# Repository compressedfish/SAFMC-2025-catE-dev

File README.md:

# SAFMC-2025-HW-Dev
meowmeowmeowmeowmeowmrowmeowmeowmeowmrowmeowmraaaaaaaaaaaaaaaaaaaaaaaaaa

pcb/keyboard     - general sensor and electronics assembly backplane thingy

pcb/cameraadapt  - testing board for OV2312/OV9782 RGB-IR camera modules

todo:
- design clip on mounting plates for cameras
- design camera mount
- test ov2312 sensor
- break out rpi5 serial interfaces

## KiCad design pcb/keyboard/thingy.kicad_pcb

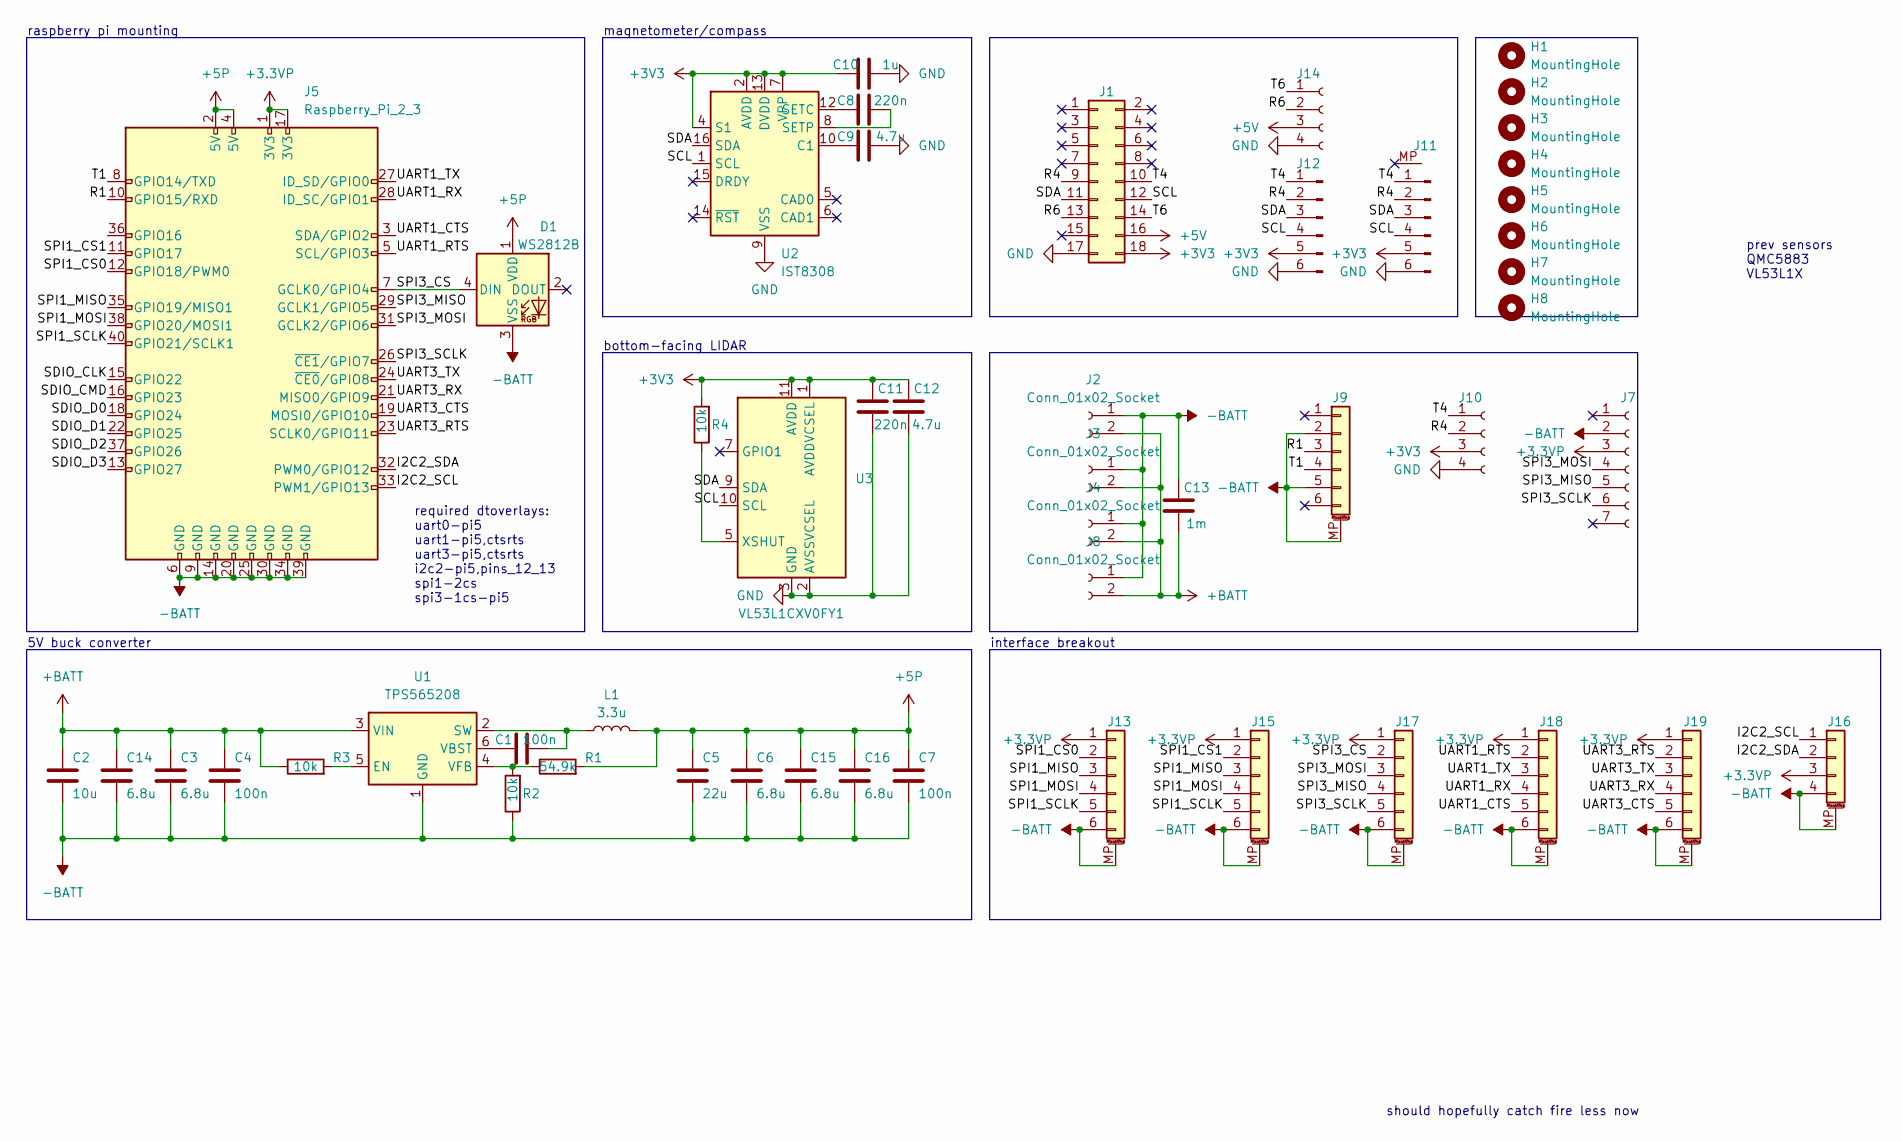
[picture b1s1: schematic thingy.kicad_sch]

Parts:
C1, C4, C7: 100n; C_0402_1005Metric
C2: 10u; CP_Elec_5x5.4
C3, C6, C14, C15, C16: 6.8u; C_0805_2012Metric
C5: 22u; CP_Elec_5x5.4
C8, C11: 220n; R_0603_1608Metric
C9, C12: 4.7u; R_0603_1608Metric
C10: 1u; R_0603_1608Metric
C13: 1m; CP_Radial_D8.0mm_P5.00mm
D1: WS2812B; LED_WS2812B-2020_PLCC4_2.0x2.0mm
H1, H2, H3, H4: MountingHole; MountingHole_2.2mm_M2
H5, H6, H7, H8: MountingHole; MountingHole_4.3mm_M4
J1: Conn_02x09_Odd_Even; PinHeader_2x09_P2.54mm_Vertical
J2, J3, J4, J8: Conn_01x02_Socket; XT-60_male
J5: Raspberry_Pi_2_3; PinSocket_2x20_P2.54mm_Horizontal
J7: Conn_01x07_Socket; PinSocket_1x07_P2.54mm_Vertical
J9: Conn_01x06_MountingPin; JST_SH_SM06B-SRSS-TB_1x06-1MP_P1.00mm_Horizontal
J10: Conn_01x04_Socket; PinHeader_1x04_P2.54mm_Vertical
J11: Conn_01x06_Pin; TE_Micro-MaTch_215079-6_2x03_P1.27mm_Vertical
J12: Conn_01x06_Pin; TE_84952-6_1x06-1MP_P1.0mm_Horizontal
J13, J15, J17, J18, J19: Conn_01x06; JST_SH_BM06B-SRSS-TB_1x06-1MP_P1.00mm_Vertical
J14: Conn_01x04_Socket; PinSocket_1x04_P2.54mm_Vertical
J16: Conn_01x04_MountingPin; JST_SH_BM04B-SRSS-TB_1x04-1MP_P1.00mm_Vertical
L1: 3.3u; L_Sunlord_MWSA0603S
R1: 54.9k; R_0402_1005Metric
R2, R3, R4: 10k; R_0402_1005Metric
U1: TPS565208; SOT-23-6
U2: IST8308; LGA-16_3x3mm_P0.5mm
U3: VL53L1CXV0FY1; ST_VL53L1x

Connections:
+3.3VP: J5.1 (3V3), J5.17 (3V3), J7.3, J13.1, J15.1, J16.3, J17.1, J18.1, J19.1
+3V3: C10.1, C11.1, C12.1, J1.18, J10.3, J11.5, J12.5, R4.2, U2.2 (AVDD), U2.4 (S1), U2.7 (VPP), U2.13 (DVDD), U3.1 (AVDDVCSEL), U3.11 (AVDD)
+5P: C5.1, C6.1, C7.1, C15.1, C16.1, D1.1 (VDD), J5.2 (5V), J5.4 (5V), L1.2, R1.2
+BATT: C2.1, C3.1, C4.1, C13.2, C14.1, J2.2, J3.2, J4.2, J8.2, R3.1, U1.3 (VIN)
-BATT: C2.2, C3.2, C4.2, C5.2, C6.2, C7.2, C13.1, C14.2, C15.2, C16.2, D1.3 (VSS), J2.1, J3.1, J4.1, J5.6 (GND), J5.9 (GND), J5.14 (GND), J5.20 (GND), J5.25 (GND), J5.30 (GND), J5.34 (GND), J5.39 (GND), J7.2, J8.1, J9.2, J9.5, J9.MP (MountPin), J13.6, J13.MP (MountPin), J15.6, J15.MP (MountPin), J16.4, J16.MP (MountPin), J17.6, J17.MP (MountPin), J18.6, J18.MP (MountPin), J19.6, J19.MP (MountPin), R2.1, U1.1 (GND)
/I2C2_SCL: J5.33 (PWM1/GPIO13), J16.1
/I2C2_SDA: J5.32 (PWM0/GPIO12), J16.2
/R1: J5.10 (GPIO15/RXD), J9.3
/R4: J1.9, J10.2, J11.2, J12.2
/R6: J1.13, J14.2
/SCL: J1.12, J11.4, J12.4, U2.1 (SCL), U3.10 (SCL)
/SDA: J1.11, J11.3, J12.3, U2.16 (SDA), U3.9 (SDA)
/SDIO_CLK: J5.15 (GPIO22)
/SDIO_CMD: J5.16 (GPIO23)
/SDIO_D0: J5.18 (GPIO24)
/SDIO_D1: J5.22 (GPIO25)
/SDIO_D2: J5.37 (GPIO26)
/SDIO_D3: J5.13 (GPIO27)
/SPI1_CS0: J5.12 (GPIO18/PWM0), J13.2
/SPI1_CS1: J5.11 (GPIO17), J15.2
/SPI1_MISO: J5.35 (GPIO19/MISO1), J13.3, J15.3
/SPI1_MOSI: J5.38 (GPIO20/MOSI1), J13.4, J15.4
/SPI1_SCLK: J5.40 (GPIO21/SCLK1), J13.5, J15.5
/SPI3_CS: D1.4 (DIN), J5.7 (GCLK0/GPIO4), J17.2
/SPI3_MISO: J5.29 (GCLK1/GPIO5), J7.5, J17.4
/SPI3_MOSI: J5.31 (GCLK2/GPIO6), J7.4, J17.3
/SPI3_SCLK: J5.26 (~CE1/GPIO7), J7.6, J17.5
/T1: J5.8 (GPIO14/TXD), J9.4
/T4: J1.10, J10.1, J11.1, J12.1
/T6: J1.14, J14.1
/UART1_CTS: J5.3 (SDA/GPIO2), J18.5
/UART1_RTS: J5.5 (SCL/GPIO3), J18.2
/UART1_RX: J5.28 (ID_SC/GPIO1), J18.4
/UART1_TX: J5.27 (ID_SD/GPIO0), J18.3
/UART3_CTS: J5.19 (MOSI0/GPIO10), J19.5
/UART3_RTS: J5.23 (SCLK0/GPIO11), J19.2
/UART3_RX: J5.21 (MISO0/GPIO9), J19.4
/UART3_TX: J5.24 (~CE0/GPIO8), J19.3
GND: C9.2, C10.2, C11.2, C12.2, J1.17, J10.4, J11.6, J12.6, J14.4, U2.9 (VSS), U2.11 (VSS), U3.2 (AVSSVCSEL), U3.3 (GND), U3.4 (GND), U3.6 (GND), U3.12 (GND)
unnamed: J1.16, J14.3
unnamed: R3.2, U1.5 (EN)
unnamed: C1.2, L1.1, U1.2 (SW)
unnamed: C1.1, U1.6 (VBST)
unnamed: R1.1, R2.2, U1.4 (VFB)
unnamed: C9.1, U2.10 (C1)
unnamed: C8.1, U2.12 (SETC)
unnamed: C8.2, U2.8 (SETP)
unnamed: R4.1, U3.5 (XSHUT)

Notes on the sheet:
prev sensors QMC5883 VL53L1X
interface breakout
raspberry pi mounting
5V buck converter
magnetometer/compass
required dtoverlays: uart0-pi5 uart1-pi5,ctsrts uart3-pi5,ctsrts i2c2-pi5,pins_12_13 spi1-2cs spi3-1cs-pi5
should hopefully catch fire less now
bottom-facing LIDAR

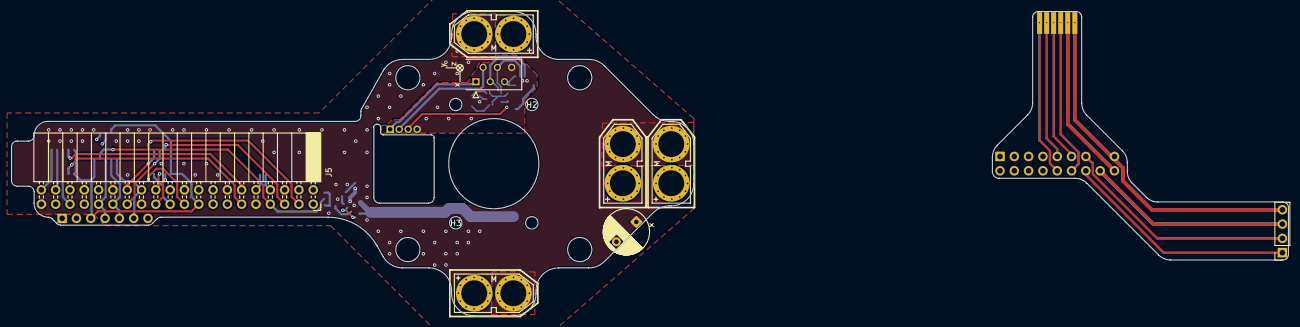
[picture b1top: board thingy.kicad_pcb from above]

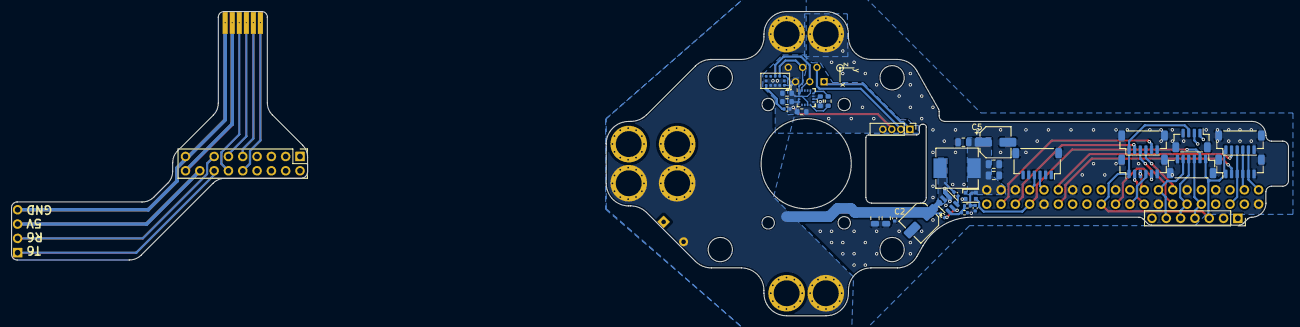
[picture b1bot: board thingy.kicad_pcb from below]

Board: 4 copper layers, 226.7 x 54.0 mm, 51 parts (34 on the bottom side), 42 nets.

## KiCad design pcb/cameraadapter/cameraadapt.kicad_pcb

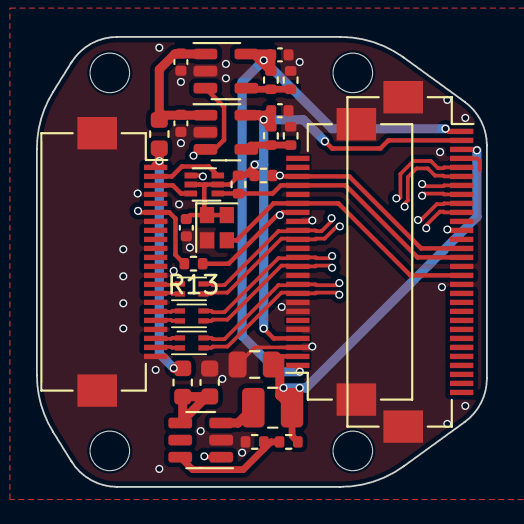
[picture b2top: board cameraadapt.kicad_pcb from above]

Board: 4 copper layers, 25.0 x 25.0 mm, 34 parts (0 on the bottom side), 24 nets.

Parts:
C1: 22u; C_0603_1608Metric
C2: 47u; C_0805_2012Metric
C3, C4, C5, C6, C7: 1u; C_0402_1005Metric
H1, H2, H3, H4: MountingHole; MountingHole_2.2mm_M2
J1: Conn_01x30_MountingPin; Hirose_FH12-30S-0.5SH_1x30-1MP_P0.50mm_Horizontal
J2: Conn_01x24_MountingPin; Hirose_FH12-24S-0.5SH_1x24-1MP_P0.50mm_Horizontal
J5: Conn_01x22_MountingPin; Hirose_FH12-22S-0.5SH_1x22-1MP_P0.50mm_Horizontal
L1, L5: L; L_0603_1608Metric
L2, L3, L4: L_Ferrite_Coupled_Small_1243; L_CommonModeChoke_Coilcraft_0603USB
L6: 2.2u; L_1008_2520Metric
Q1: DMG1024UV; SOT-563
R1, R2, R3, R4, R5, R6: R; R_0402_1005Metric
R7, R8: 2k2; R_0402_1005Metric
R13: 0; R_0402_1005Metric
U1: AP3429K; TSOT-23-6
U3, U4: ADP123; TSOT-23-5
X1: 27MHz; Crystal_SMD_2016-4Pin_2.0x1.6mm

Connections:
+1V2: C2.1, J1.3, J2.2, L6.2, R1.1
+1V8: C3.1, C7.1, J1.2, J2.4, Q1.2 (G1), Q1.5 (G2), R5.1, R7.1, R8.1, U4.5 (VOUT), X1.1 (Tri-State), X1.4 (VDD)
+2V8: C6.1, J1.1, J2.1, R3.1, U3.5 (VOUT)
+3.3V: J5.1, L1.1, L5.1
/EN: J5.6, R13.2, U1.1 (EN), U3.3 (EN), U4.3 (EN)
/MCLK: J1.17, J2.19, X1.3 (OUT)
/MCLK_N: J1.8, J2.15, J5.15, L4.1, L4.2
/MCLK_P: J1.7, J2.16, J5.14, L4.3, L4.4
/MD0_N: J1.10, J2.9, J5.21, L2.1, L2.2
/MD0_P: J1.9, J2.10, J5.20, L2.3, L2.4
/MD1_N: J1.6, J2.12, J5.18, L3.1, L3.2
/MD1_P: J1.5, J2.13, J5.17, L3.3, L3.4
/SCL: J5.3, Q1.6 (D1)
/SCL_1V8: J1.15, J2.21, Q1.1 (S1), R7.2
/SDA: J5.2, Q1.3 (D2)
/SDA_1V8: J1.14, J2.22, Q1.4 (S2), R8.2
/XSHUTDOWN: J1.12, J2.18, R13.1
GND: C1.2, C2.2, C3.2, C4.2, C5.2, C6.2, C7.2, J1.4, J1.11, J1.16, J1.18, J1.MP (MountPin), J2.3, J2.5, J2.7, J2.8, J2.11, J2.14, J2.17, J2.20, J2.MP (MountPin), J5.4, J5.7, J5.10, J5.13, J5.16, J5.19, J5.22, J5.MP (MountPin), R2.2, R4.2, R6.2, U1.2 (GND), U3.2 (GND), U4.2 (GND), X1.2 (GND)
unnamed: R1.2, R2.1, U1.6 (FB)
unnamed: L6.1, U1.3 (LX)
unnamed: C1.1, L1.2, U1.4 (VIN)
unnamed: R3.2, R4.1, U3.4 (SENSE/ADJ)
unnamed: C4.1, C5.1, L5.2, U3.1 (VIN), U4.1 (VIN)
unnamed: R5.2, R6.1, U4.4 (SENSE/ADJ)

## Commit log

2024-09-23 Create h
2024-09-23 how what
2024-09-25 better organisation
    adapting repo to only catE dev
2024-09-27 placement verification
2024-10-08 beginning schematic cleanup
2024-10-08 before tomfoolery
2024-11-11 mech
2024-11-14 update frame
    before pruning the assembly
2024-11-14 frame v02
    cleaned up the main assembly
2024-11-14 thingy
    add keyboard mechanical file
2024-11-18 frame v02
    adding production files
2024-12-11 update frame v04
2024-12-11 tidy up keyboard
    tidy up keyboard schematic and break out pi serial interfaces
2024-12-13 update pcb production files
2025-02-20 update mechanical
